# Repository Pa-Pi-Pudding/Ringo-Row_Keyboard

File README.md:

# Ringo-Row_Keyboard

## parts list
|name|rated value|number of articles|remarks|
|----|----|----|----|
|type-c connector|5v 12 pin| 2|http://akizukidenshi.com/catalog/g/gC-14356/|
|PolySwitch|1.35A | 2|http://akizukidenshi.com/catalog/g/gP-13013/|
|PRTR5V0U2X SOT-143|1GHz| 2|https://www.aitendo.com/product/15987|
|resistor|22 Ω| 4||
|resistor|5.1K Ω| 4||
|ResetSwitch| | 1| https://www.aitendo.com/product/10524|
|resistor | 10k Ω | 1 | |
|Crystal oscillator| 16Mhz 4pin| 1|http://akizukidenshi.com/catalog/g/gP-02457/|
|Chip capacitor | 22pF 1206 | 2| https://www.aitendo.com/product/15403|
|Chip capacitor | 0.1μF 1206| 3| http://akizukidenshi.com/catalog/g/gP-15180/|
|Chip capacitor | 1μF 1206 | 1| http://akizukidenshi.com/catalog/g/gP-15180/|
|Chip capacitor | 10μF 1206 | 1| http://akizukidenshi.com/catalog/g/gP-15180/|
|resistor | 1k Ω | 1 | |
|switching diode|100v 200mA| 72|http://akizukidenshi.com/catalog/g/gI-07783/|
|ATMega42u4 AUR| 5v| 1| http://akizukidenshi.com/catalog/g/gI-09835/|

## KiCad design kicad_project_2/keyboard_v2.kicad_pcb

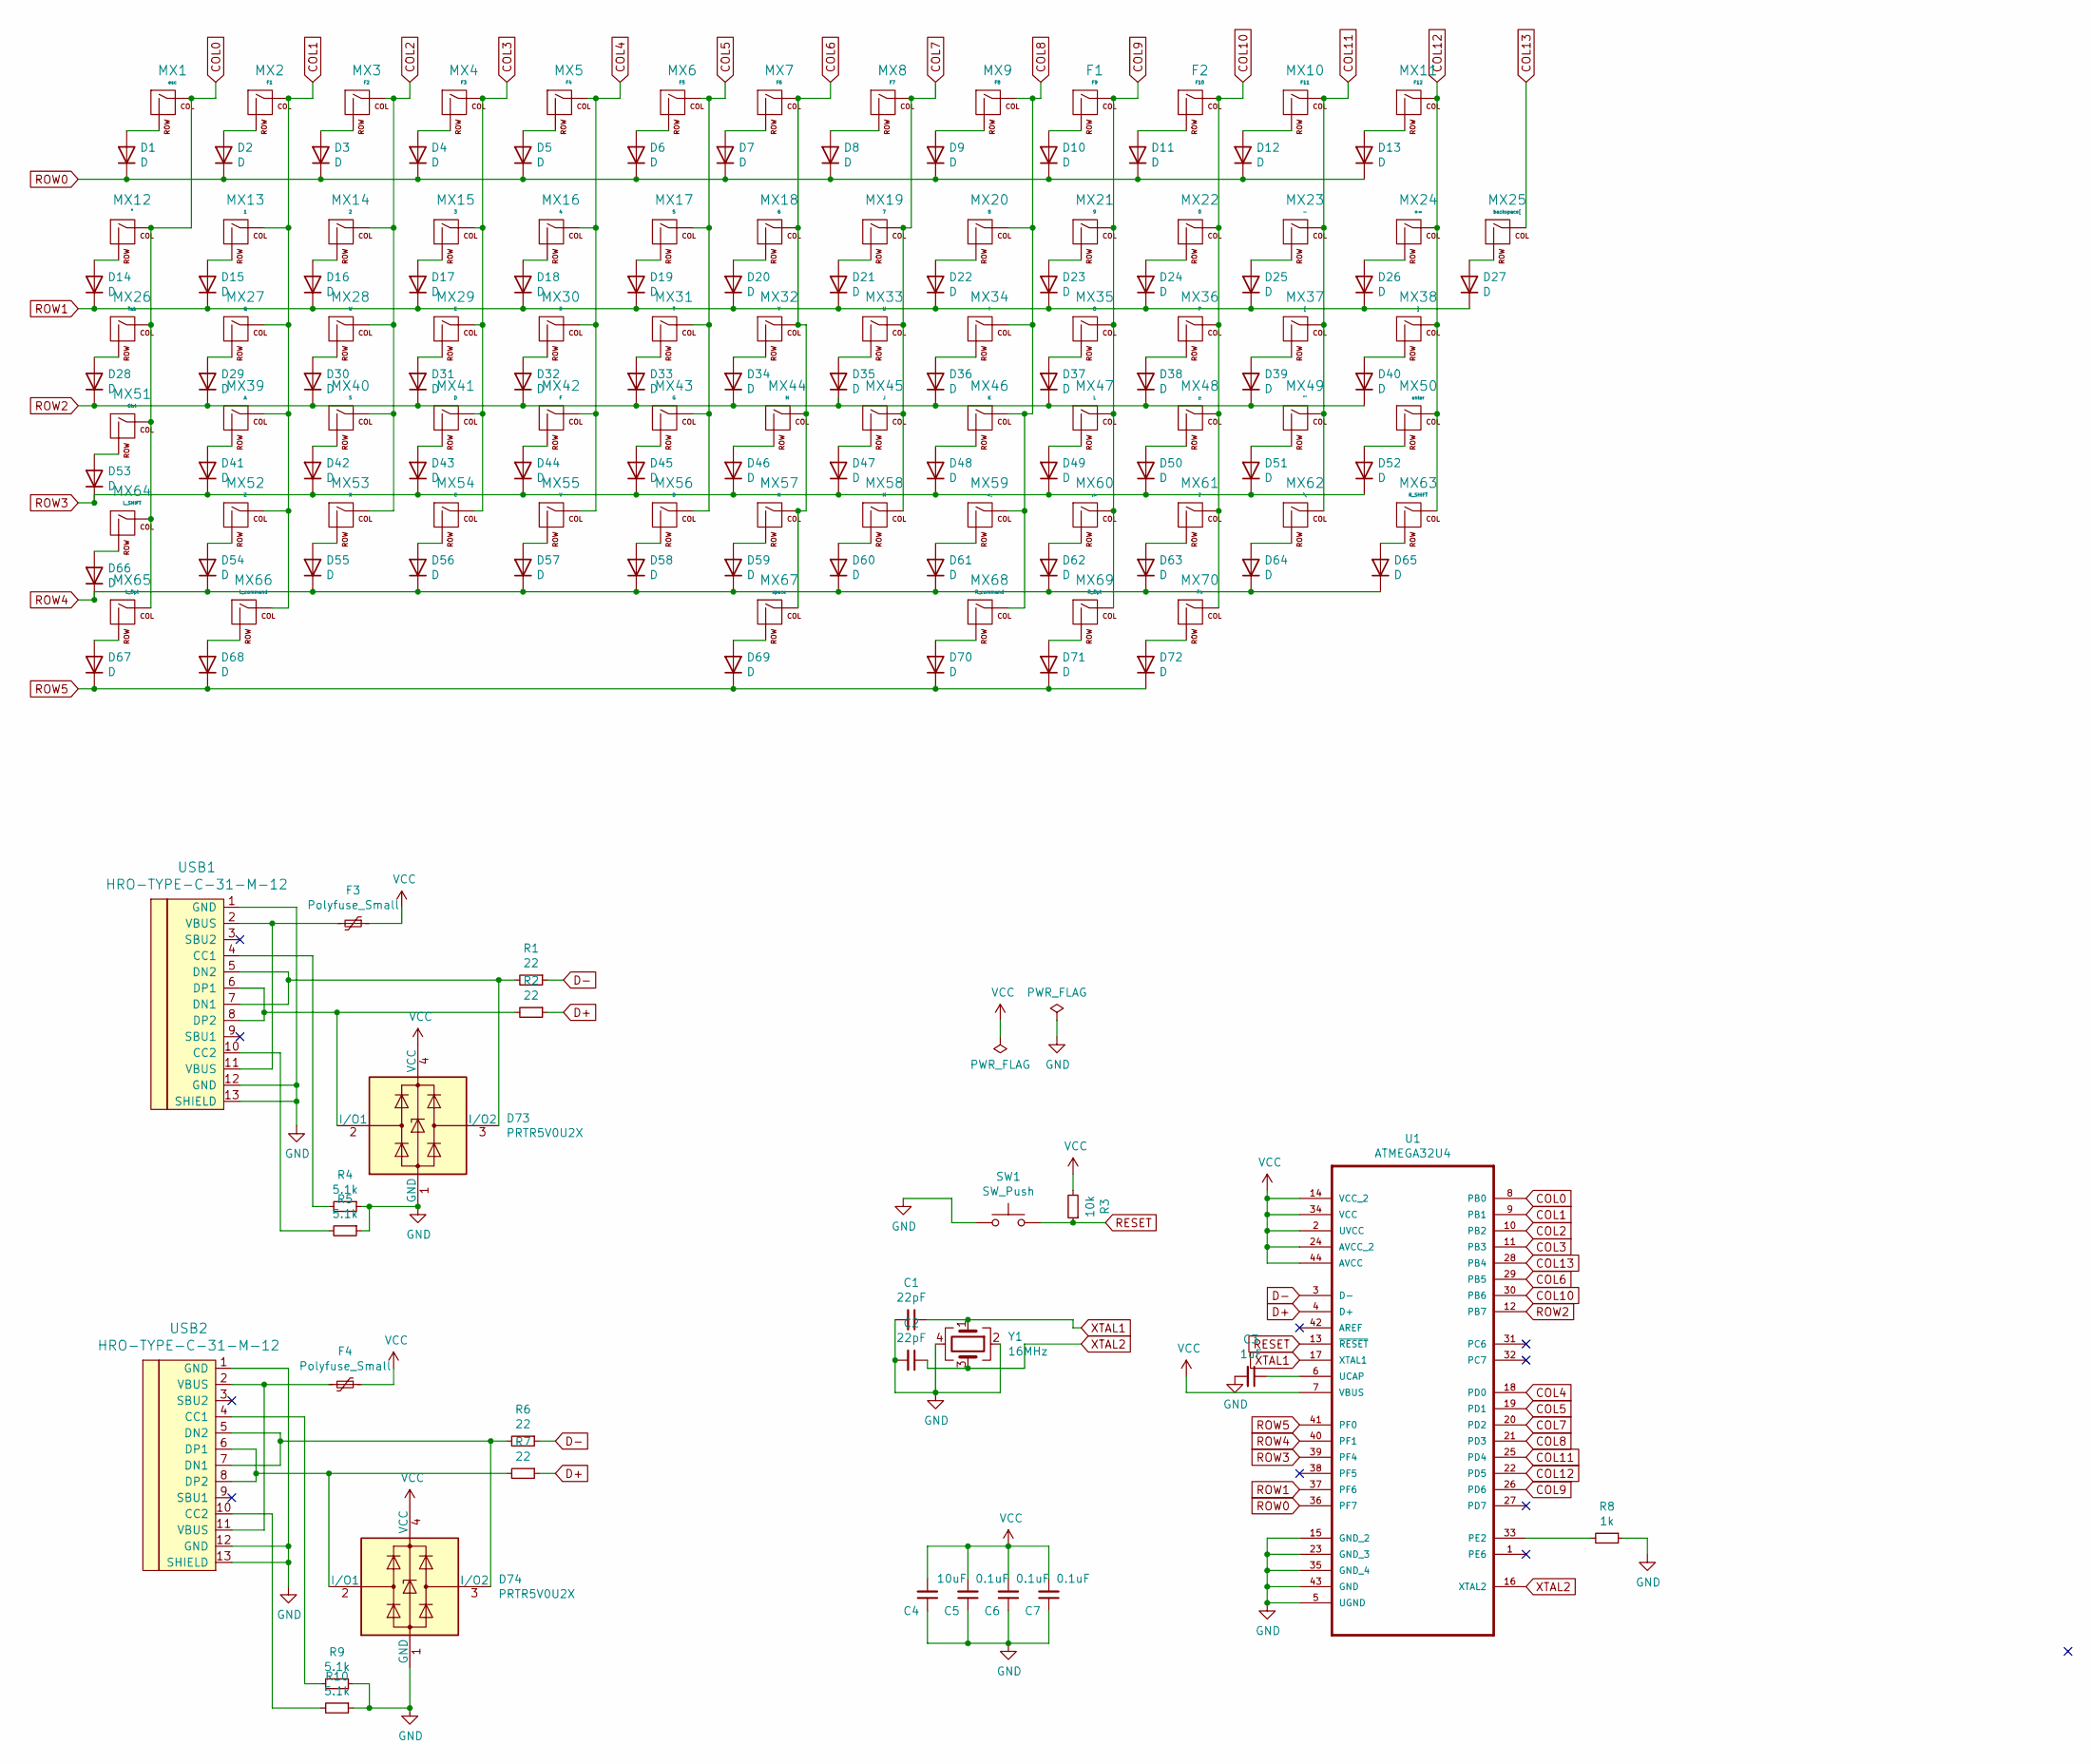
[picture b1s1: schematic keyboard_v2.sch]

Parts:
C1, C2: 22pF; C_1206_3216Metric_Pad1.42x1.75mm_HandSolder
C3: 1uF; D3_TH_SMD
C4: 10uF; D3_TH_SMD
C5, C6, C7: 0.1uF; D3_TH_SMD
D1, D2, D3, D4, D5, D6, D7, D8, D9, D10, D11, D12, D13, D14, D15, D16, D17, D18, D19, D20, D21, D22, D23, D24, D25, D26, D27, D28, D29, D30, D31, D32, D33, D34, D35, D36, D37, D38, D39, D40, D41, D42, D43, D44, D45, D46, D47, D48, D49, D50, D51, D52, D53, D54, D55, D56, D57, D58, D59, D60, D61, D62, D63, D64, D65, D66, D67, D68, D69, D70, D71, D72: D; D3_TH_SMD
D73, D74: PRTR5V0U2X; SOT-143_Handsoldering
F1: F9; ALPS-1U
F2: F10; ALPS-1U
F3, F4: Polyfuse_Small; D3_TH_SMD
MX1: esc; ALPS-1U
MX2: F1; ALPS-1U
MX3: F2; ALPS-1U
MX4: F3; ALPS-1U
MX5: F4; ALPS-1U
MX6: F5; ALPS-1U
MX7: F6; ALPS-1U
MX8: F7; ALPS-1U
MX9: F8; ALPS-1U
MX10: F11; ALPS-1U
MX11: F12; ALPS-1U
MX12: ~^; ALPS-1U
MX13: 1; ALPS-1U
MX14: 2; ALPS-1U
MX15: 3; ALPS-1U
MX16: 4; ALPS-1U
MX17: 5; ALPS-1U
MX18: 6; ALPS-1U
MX19: 7; ALPS-1U
MX20: 8; ALPS-1U
MX21: 9; ALPS-1U
MX22: 0; ALPS-1U
MX23: -; ALPS-1U
MX24: +=; ALPS-1U
MX25: backspace[; ALPS-1U
MX26: Tab; ALPS-1U
MX27: Q; ALPS-1U
MX28: W; ALPS-1U
MX29: E; ALPS-1U
MX30: R; ALPS-1U
MX31: T; ALPS-1U
MX32: Y; ALPS-1U
MX33: U; ALPS-1U
MX34: I; ALPS-1U
MX35: O; ALPS-1U
MX36: P; ALPS-1U
MX37: [; ALPS-1U
MX38: ]; ALPS-1U
MX39: A; ALPS-1U
MX40: S; ALPS-1U
MX41: D; ALPS-1U
MX42: F; ALPS-1U
MX43: G; ALPS-1U
MX44: H; ALPS-1U
MX45: J; ALPS-1U
MX46: K; ALPS-1U
MX47: L; ALPS-1U
MX48: :;; ALPS-1U
MX49: \"'; ALPS-1U
MX50: enter; ALPS-1U
MX51: Ctrl; ALPS-1U
MX52: Z; ALPS-1U
MX53: X; ALPS-1U
MX54: C; ALPS-1U
MX55: V; ALPS-1U
MX56: B; ALPS-1U
MX57: N; ALPS-1U
MX58: M; ALPS-1U
MX59: <,; ALPS-1U
MX60: .>; ALPS-1U
MX61: ?; ALPS-1U
MX62: \\; ALPS-1U
MX63: R_SHIFT; ALPS-1U
MX64: L_SHIFT; ALPS-1U
MX65: L_Opt; ALPS-1U
MX66: L_command; ALPS-1U
MX67: space; ALPS-1U
MX68: R_command; ALPS-1U
MX69: R_Opt; ALPS-1U
MX70: Fn; ALPS-1U
R1, R2, R6, R7: 22; D3_TH_SMD
R3: 10k; D3_TH_SMD
R4, R5, R9, R10: 5.1k; D3_TH_SMD
R8: 1k; D3_TH_SMD
SW1: SW_Push; SW_Tactile_SPST_Angled_PTS645Vx39-2LFS
U1: ATMEGA32U4; ATmega32U4
USB1, USB2: HRO-TYPE-C-31-M-12; HRO-TYPE-C-31-M-12-HandSoldering
Y1: 16MHz; Crystal_SMD_3225-4Pin_3.2x2.5mm_HandSoldering

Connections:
COL0: MX1.1 (COL), MX12.1 (COL), MX26.1 (COL), MX51.1 (COL), MX64.1 (COL), MX65.1 (COL), U1.8 (PB0)
COL1: MX2.1 (COL), MX13.1 (COL), MX27.1 (COL), MX39.1 (COL), MX52.1 (COL), MX66.1 (COL), U1.9 (PB1)
COL2: MX3.1 (COL), MX14.1 (COL), MX28.1 (COL), MX40.1 (COL), MX53.1 (COL), U1.10 (PB2)
COL3: MX4.1 (COL), MX15.1 (COL), MX29.1 (COL), MX41.1 (COL), MX54.1 (COL), U1.11 (PB3)
COL4: MX5.1 (COL), MX16.1 (COL), MX30.1 (COL), MX42.1 (COL), MX55.1 (COL), U1.18 (PD0)
COL5: MX6.1 (COL), MX17.1 (COL), MX31.1 (COL), MX43.1 (COL), MX56.1 (COL), U1.19 (PD1)
COL6: MX7.1 (COL), MX18.1 (COL), MX32.1 (COL), MX44.1 (COL), MX57.1 (COL), MX67.1 (COL), U1.29 (PB5)
COL7: MX8.1 (COL), MX19.1 (COL), MX33.1 (COL), MX45.1 (COL), MX58.1 (COL), U1.20 (PD2)
COL8: MX9.1 (COL), MX20.1 (COL), MX34.1 (COL), MX46.1 (COL), MX59.1 (COL), MX68.1 (COL), U1.21 (PD3)
COL9: F1.1 (COL), MX21.1 (COL), MX35.1 (COL), MX47.1 (COL), MX60.1 (COL), MX69.1 (COL), U1.26 (PD6)
COL10: F2.1 (COL), MX22.1 (COL), MX36.1 (COL), MX48.1 (COL), MX61.1 (COL), MX70.1 (COL), U1.30 (PB6)
COL11: MX10.1 (COL), MX23.1 (COL), MX37.1 (COL), MX49.1 (COL), MX62.1 (COL), U1.25 (PD4)
COL12: MX11.1 (COL), MX24.1 (COL), MX38.1 (COL), MX50.1 (COL), MX63.1 (COL), U1.22 (PD5)
COL13: MX25.1 (COL), U1.28 (PB4)
D+: R2.1, R7.1, U1.4 (D+)
D-: R1.1, R6.1, U1.3 (D-)
GND: C1.2, C2.2, C3.2, C4.1, C5.1, C6.1, C7.1, D73.1 (GND), D74.1 (GND), R4.1, R5.1, R8.1, R9.1, R10.1, SW1.1, U1.5 (UGND), U1.15 (GND_2), U1.23 (GND_3), U1.35 (GND_4), U1.43 (GND), USB1.1 (GND), USB1.12 (GND), USB1.13 (SHIELD), USB2.1 (GND), USB2.12 (GND), USB2.13 (SHIELD), Y1.2, Y1.4
unnamed: C3.1, U1.6 (UCAP)
unnamed: D1.2 (A), MX1.2 (ROW)
unnamed: D2.2 (A), MX2.2 (ROW)
unnamed: D3.2 (A), MX3.2 (ROW)
unnamed: D4.2 (A), MX4.2 (ROW)
unnamed: D5.2 (A), MX5.2 (ROW)
unnamed: D6.2 (A), MX6.2 (ROW)
unnamed: D7.2 (A), MX7.2 (ROW)
unnamed: D8.2 (A), MX8.2 (ROW)
unnamed: D9.2 (A), MX9.2 (ROW)
unnamed: D10.2 (A), F1.2 (ROW)
unnamed: D11.2 (A), F2.2 (ROW)
unnamed: D12.2 (A), MX10.2 (ROW)
unnamed: D13.2 (A), MX11.2 (ROW)
unnamed: D14.2 (A), MX12.2 (ROW)
unnamed: D15.2 (A), MX13.2 (ROW)
unnamed: D16.2 (A), MX14.2 (ROW)
unnamed: D17.2 (A), MX15.2 (ROW)
unnamed: D18.2 (A), MX16.2 (ROW)
unnamed: D19.2 (A), MX17.2 (ROW)
unnamed: D20.2 (A), MX18.2 (ROW)
unnamed: D21.2 (A), MX19.2 (ROW)
unnamed: D22.2 (A), MX20.2 (ROW)
unnamed: D23.2 (A), MX21.2 (ROW)
unnamed: D24.2 (A), MX22.2 (ROW)
unnamed: D25.2 (A), MX23.2 (ROW)
unnamed: D26.2 (A), MX24.2 (ROW)
unnamed: D27.2 (A), MX25.2 (ROW)
unnamed: D28.2 (A), MX26.2 (ROW)
unnamed: D29.2 (A), MX27.2 (ROW)
unnamed: D30.2 (A), MX28.2 (ROW)
unnamed: D31.2 (A), MX29.2 (ROW)
unnamed: D32.2 (A), MX30.2 (ROW)
unnamed: D33.2 (A), MX31.2 (ROW)
unnamed: D34.2 (A), MX32.2 (ROW)
unnamed: D35.2 (A), MX33.2 (ROW)
unnamed: D36.2 (A), MX34.2 (ROW)
unnamed: D37.2 (A), MX35.2 (ROW)
unnamed: D38.2 (A), MX36.2 (ROW)
unnamed: D39.2 (A), MX37.2 (ROW)
unnamed: D40.2 (A), MX38.2 (ROW)
unnamed: D41.2 (A), MX39.2 (ROW)
unnamed: D42.2 (A), MX40.2 (ROW)
unnamed: D43.2 (A), MX41.2 (ROW)
unnamed: D44.2 (A), MX42.2 (ROW)
unnamed: D45.2 (A), MX43.2 (ROW)
unnamed: D46.2 (A), MX44.2 (ROW)
unnamed: D47.2 (A), MX45.2 (ROW)
unnamed: D48.2 (A), MX46.2 (ROW)
unnamed: D49.2 (A), MX47.2 (ROW)
unnamed: D50.2 (A), MX48.2 (ROW)
unnamed: D51.2 (A), MX49.2 (ROW)
unnamed: D52.2 (A), MX50.2 (ROW)
unnamed: D53.2 (A), MX51.2 (ROW)
unnamed: D54.2 (A), MX52.2 (ROW)
unnamed: D55.2 (A), MX53.2 (ROW)
unnamed: D56.2 (A), MX54.2 (ROW)
unnamed: D57.2 (A), MX55.2 (ROW)
unnamed: D58.2 (A), MX56.2 (ROW)
unnamed: D59.2 (A), MX57.2 (ROW)
unnamed: D60.2 (A), MX58.2 (ROW)
unnamed: D61.2 (A), MX59.2 (ROW)
unnamed: D62.2 (A), MX60.2 (ROW)
unnamed: D63.2 (A), MX61.2 (ROW)
unnamed: D64.2 (A), MX62.2 (ROW)
unnamed: D65.2 (A), MX63.2 (ROW)
unnamed: D66.2 (A), MX64.2 (ROW)
unnamed: D67.2 (A), MX65.2 (ROW)
unnamed: D68.2 (A), MX66.2 (ROW)
unnamed: D69.2 (A), MX67.2 (ROW)
unnamed: D70.2 (A), MX68.2 (ROW)
unnamed: D71.2 (A), MX69.2 (ROW)
unnamed: D72.2 (A), MX70.2 (ROW)
unnamed: D73.2 (I/O1), R2.2, USB1.6 (DP1), USB1.8 (DP2)
unnamed: D73.3 (I/O2), R1.2, USB1.5 (DN2), USB1.7 (DN1)
unnamed: D74.2 (I/O1), R7.2, USB2.6 (DP1), USB2.8 (DP2)
unnamed: D74.3 (I/O2), R6.2, USB2.5 (DN2), USB2.7 (DN1)
unnamed: F3.2, USB1.2 (VBUS), USB1.11 (VBUS)
unnamed: F4.2, USB2.2 (VBUS), USB2.11 (VBUS)
unnamed: R4.2, USB1.4 (CC1)
unnamed: R5.2, USB1.10 (CC2)
unnamed: R8.2, U1.33 (PE2)
unnamed: R9.2, USB2.4 (CC1)
unnamed: R10.2, USB2.10 (CC2)
RESET: R3.1, SW1.2, U1.13 (~RESET)
ROW0: D1.1 (K), D2.1 (K), D3.1 (K), D4.1 (K), D5.1 (K), D6.1 (K), D7.1 (K), D8.1 (K), D9.1 (K), D10.1 (K), D11.1 (K), D12.1 (K), D13.1 (K), U1.36 (PF7)
ROW1: D14.1 (K), D15.1 (K), D16.1 (K), D17.1 (K), D18.1 (K), D19.1 (K), D20.1 (K), D21.1 (K), D22.1 (K), D23.1 (K), D24.1 (K), D25.1 (K), D26.1 (K), D27.1 (K), U1.37 (PF6)
ROW2: D28.1 (K), D29.1 (K), D30.1 (K), D31.1 (K), D32.1 (K), D33.1 (K), D34.1 (K), D35.1 (K), D36.1 (K), D37.1 (K), D38.1 (K), D39.1 (K), D40.1 (K), U1.12 (PB7)
ROW3: D41.1 (K), D42.1 (K), D43.1 (K), D44.1 (K), D45.1 (K), D46.1 (K), D47.1 (K), D48.1 (K), D49.1 (K), D50.1 (K), D51.1 (K), D52.1 (K), D53.1 (K), U1.39 (PF4)
ROW4: D54.1 (K), D55.1 (K), D56.1 (K), D57.1 (K), D58.1 (K), D59.1 (K), D60.1 (K), D61.1 (K), D62.1 (K), D63.1 (K), D64.1 (K), D65.1 (K), D66.1 (K), U1.40 (PF1)
ROW5: D67.1 (K), D68.1 (K), D69.1 (K), D70.1 (K), D71.1 (K), D72.1 (K), U1.41 (PF0)
VCC: C4.2, C5.2, C6.2, C7.2, D73.4 (VCC), D74.4 (VCC), F3.1, F4.1, R3.2, U1.2 (UVCC), U1.7 (VBUS), U1.14 (VCC_2), U1.24 (AVCC_2), U1.34 (VCC), U1.44 (AVCC)
XTAL1: C1.1, U1.17 (XTAL1), Y1.1
XTAL2: C2.1, U1.16 (XTAL2), Y1.3

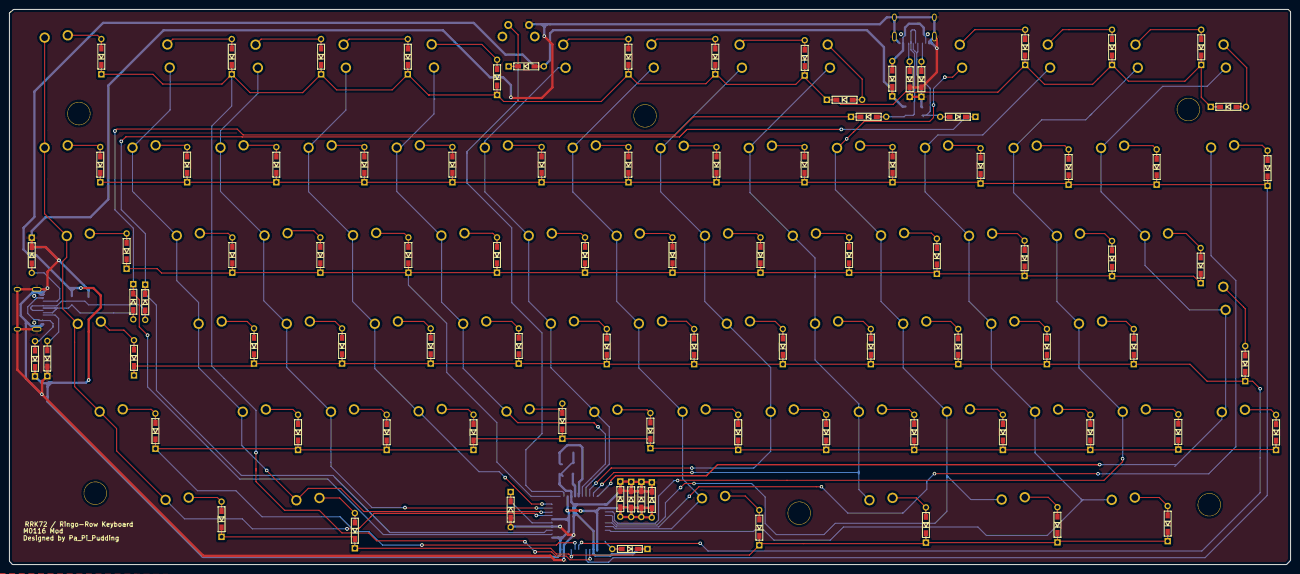
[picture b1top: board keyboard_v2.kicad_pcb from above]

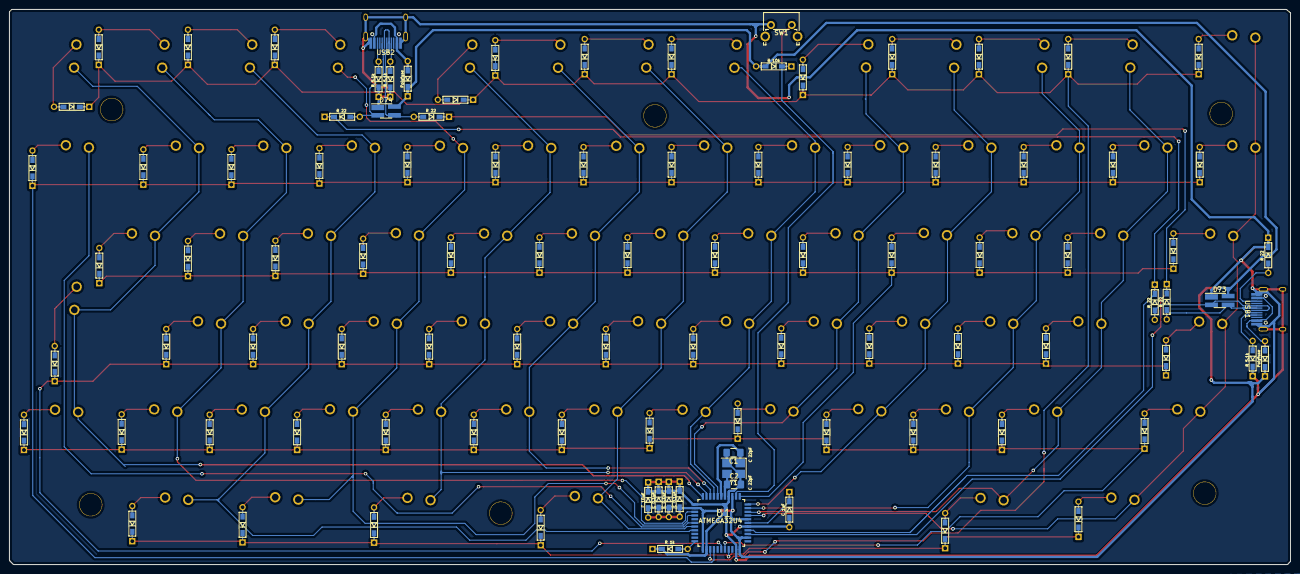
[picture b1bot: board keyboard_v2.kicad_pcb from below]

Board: 2 copper layers, 277.2 x 120.1 mm, 176 parts (97 on the bottom side), 111 nets.

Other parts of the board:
-: Val**; HOLE
.: Val**; HOLE
Ref**: Val**; HOLE
Ref**#2, Ref**#3, Ref**#4: Val**; HOLE

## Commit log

2020-07-19 fix readme
2020-07-19 fix pcb
2020-08-01 add dxf
2020-08-28 fix parts list
2024-08-14 add keymap
